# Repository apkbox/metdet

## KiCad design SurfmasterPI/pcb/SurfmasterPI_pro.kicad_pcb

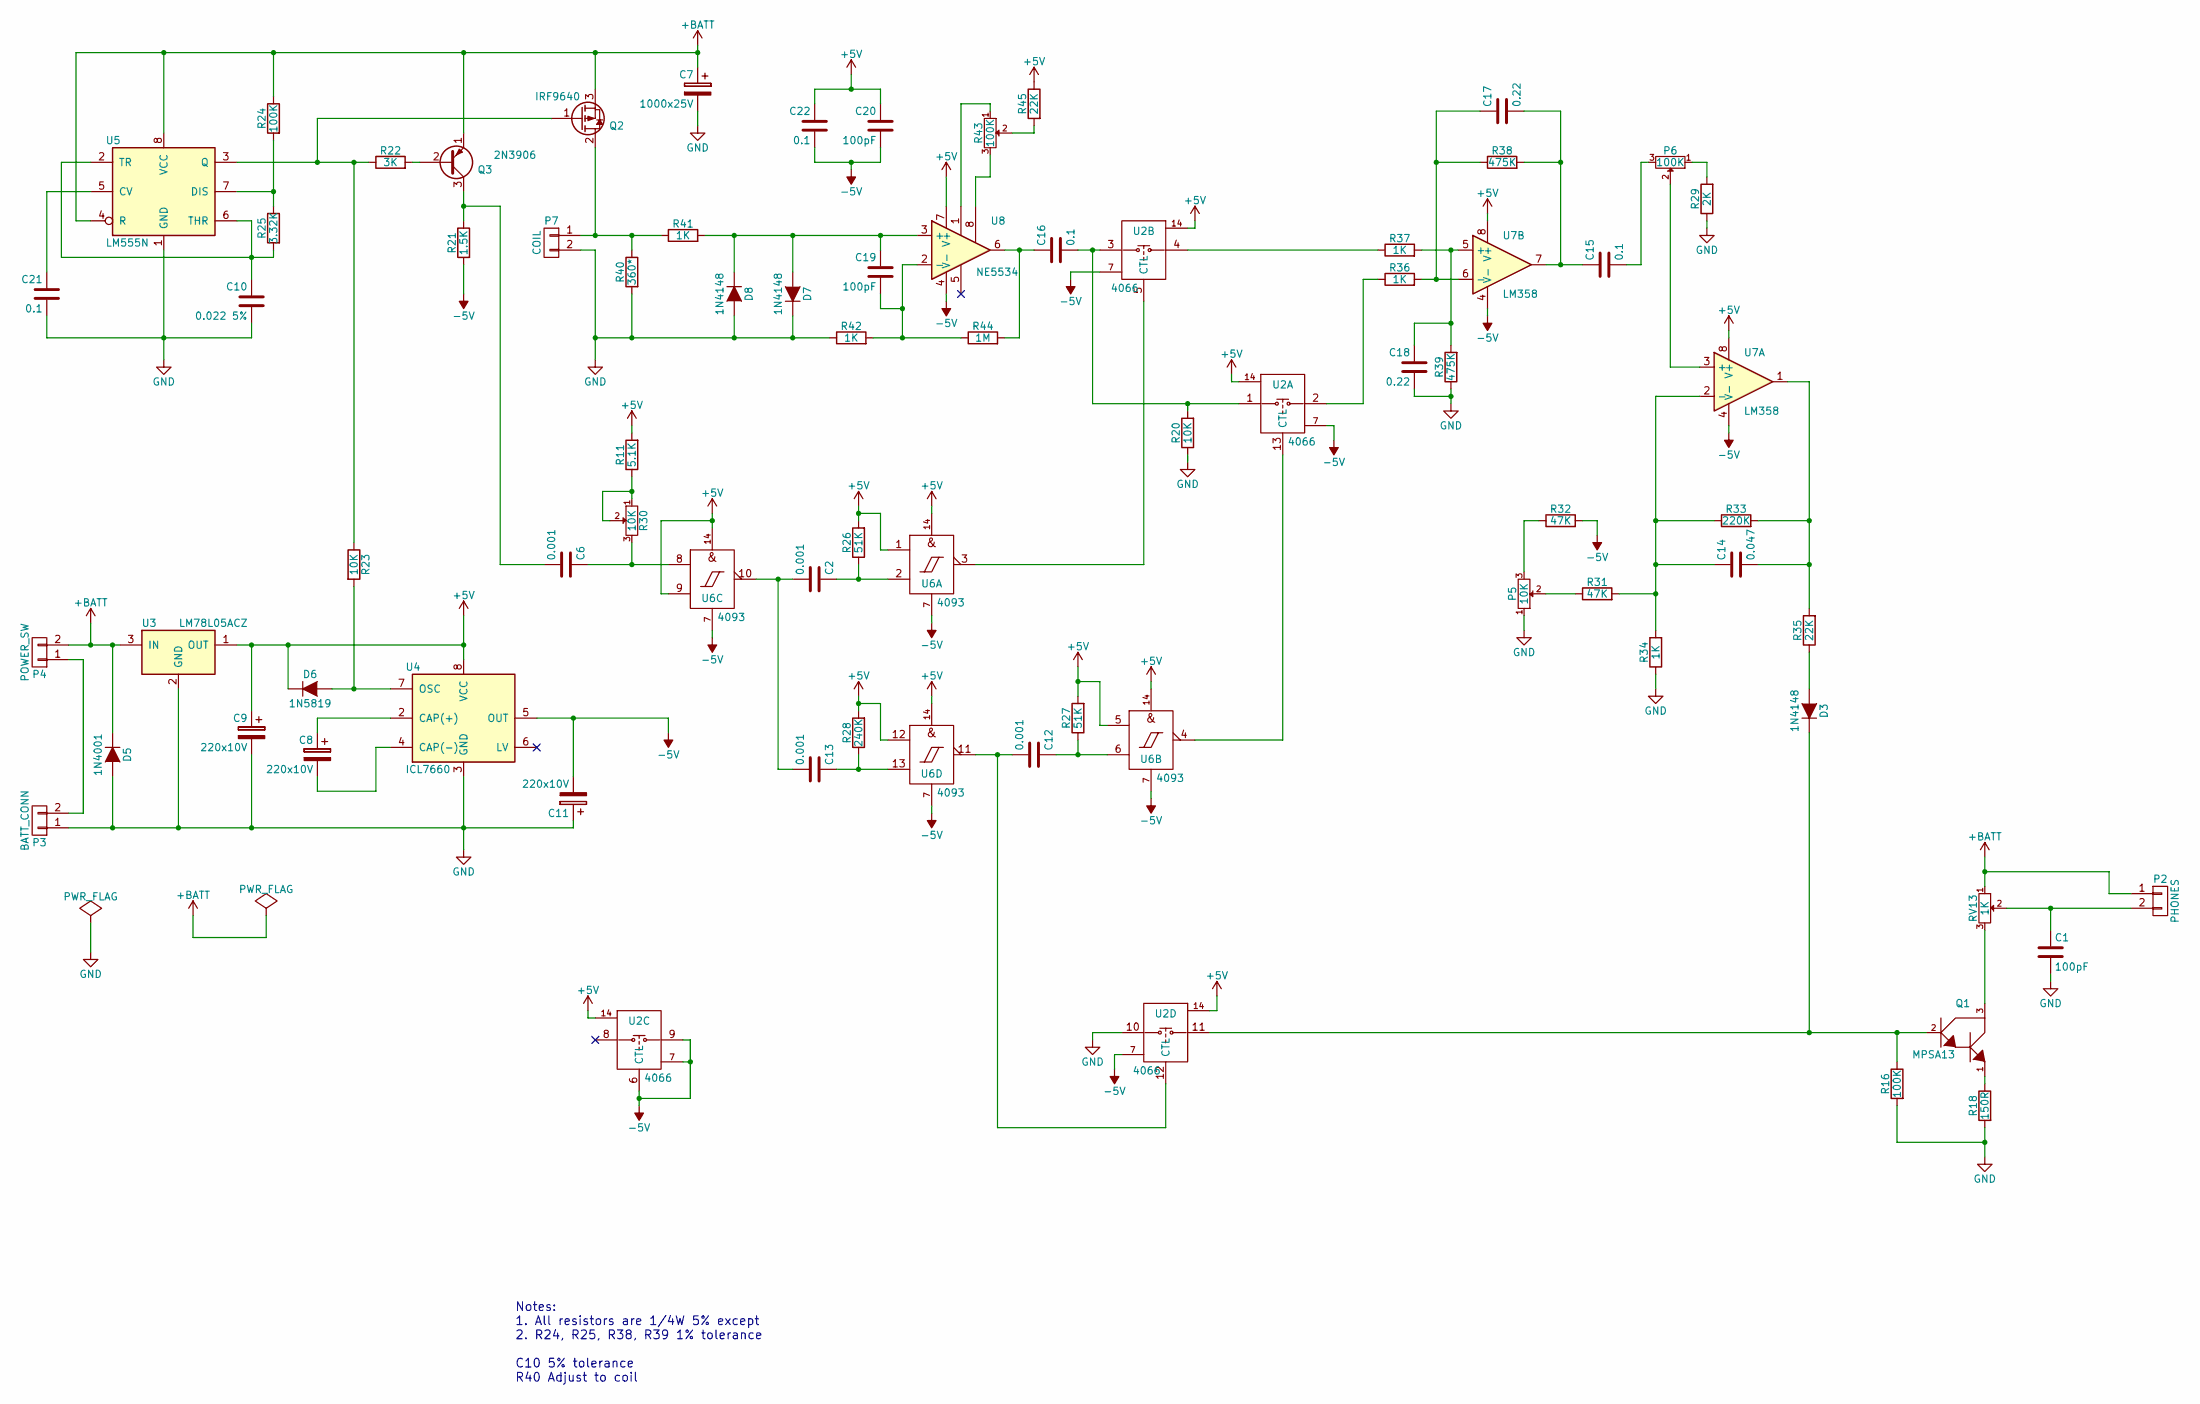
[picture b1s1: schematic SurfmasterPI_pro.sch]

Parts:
C1, C19, C20: 100pF; C_Disc_D3_P2.5
C2, C6, C12, C13: 0.001; C_Disc_D6_P5
C7: 1000x25V; C_Radial_D13_L21_P5
C8, C9, C11: 220x10V; C_Radial_D7.5_L11.2_P2.5
C10: 0.022 5%; C_Disc_D6_P5
C14: 0.047; C_Disc_D6_P5
C15, C16, C21, C22: 0.1; C_Disc_D6_P5
C17, C18: 0.22; C_Disc_D6_P5
D3, D7, D8: 1N4148; Diode_DO-41_SOD81_Horizontal_RM10
D5: 1N4001; Diode_DO-35_SOD27_Horizontal_RM10
D6: 1N5819; Diode_DO-35_SOD27_Horizontal_RM10
P2: PHONES; Pin_Header_Straight_1x02
P3: BATT_CONN; Pin_Header_Straight_1x02
P4: POWER_SW; Pin_Header_Straight_1x02
P5: 10K; Potentiometer_WirePads_Small
P6: 100K; Potentiometer_WirePads_Small
P7: COIL; Pin_Header_Straight_1x02
Q1: MPSA13; TO-92_Molded_Narrow
Q2: IRF9640; TO-220_Neutral123_Vertical_LargePads
Q3: 2N3906; TO-92_Molded_Narrow
R11: 5.1K; Resistor_Horizontal_RM10mm
R16, R24: 100K; Resistor_Horizontal_RM10mm
R18: 150R; Resistor_Horizontal_RM10mm
R20, R23: 10K; Resistor_Horizontal_RM10mm
R21: 1.5K; Resistor_Horizontal_RM10mm
R22: 3K; Resistor_Horizontal_RM10mm
R25: 3.32K; Resistor_Horizontal_RM10mm
R26, R27: 51K; Resistor_Horizontal_RM10mm
R28: 240K; Resistor_Horizontal_RM10mm
R29: 2K; Resistor_Horizontal_RM10mm
R30: 10K; Potentiometer_Trimmer-Suntan-TSR-3386P
R31, R32: 47K; Resistor_Horizontal_RM10mm
R33: 220K; Resistor_Horizontal_RM10mm
R34, R36, R37, R41, R42: 1K; Resistor_Horizontal_RM10mm
R35, R45: 22K; Resistor_Horizontal_RM10mm
R38, R39: 475K; Resistor_Horizontal_RM10mm
R40: 360*; Resistor_Horizontal_RM10mm
R43: 100K; Potentiometer_Trimmer-Suntan-TSR-3386P
R44: 1M; Resistor_Horizontal_RM10mm
RV13: 1K; Potentiometer_WirePads_Small
U2: 4066; DIP-14_W7.62mm_LongPads
U3: LM78L05ACZ; TO-92_Molded_Narrow
U4: ICL7660; DIP-8_W7.62mm_LongPads
U5: LM555N; DIP-8_W7.62mm_LongPads
U6: 4093; DIP-14_W7.62mm_LongPads
U7: LM358; DIP-8_W7.62mm_LongPads
U8: NE5534; DIP-8_W7.62mm_LongPads

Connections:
+5V: C9.1, C20.1, C22.1, D6.1 (K), R11.2, R26.2, R27.2, R28.2, R45.1, U2.14, U3.1 (OUT), U4.8 (VCC), U6.1, U6.5, U6.9, U6.12, U6.14, U7.8 (V+), U8.7 (V+)
+BATT: C7.1, D5.1 (K), P2.1, P4.2, Q2.3 (S), Q3.1 (E), R24.1, RV13.1, U3.3 (IN), U5.4 (R), U5.8 (VCC)
-5V: C11.2, C20.2, C22.2, R21.2, R32.2, U2.6 (CTL), U2.7, U2.9, U4.5 (OUT), U6.7, U7.4 (V-), U8.4 (V-)
GND: C1.2, C7.2, C9.2, C10.2, C11.1, C18.2, C21.2, D5.2 (A), D7.1 (K), D8.2 (A), P3.1, P5.1, P7.2, R16.2, R18.2, R20.1, R29.1, R34.1, R39.1, R40.2, R42.1, U2.10, U3.2 (GND), U4.3 (GND), U5.1 (GND)
unnamed: C1.1, P2.2, RV13.2
unnamed: C2.1, R26.1, U6.2
unnamed: C6.1, R30.3, U6.8
unnamed: C6.2, Q3.3 (C), R21.1
unnamed: C8.1, U4.2 (CAP(+))
unnamed: C8.2, U4.4 (CAP(-))
unnamed: C10.1, R25.2, U5.2 (TR), U5.6 (THR)
unnamed: C12.1, R27.1, U6.6
unnamed: C12.2, U2.12 (CTL), U6.11
unnamed: C13.1, R28.1, U6.13
unnamed: C2.2, C13.2, U6.10
unnamed: C14.1, R31.2, R33.1, R34.2, U7.2 (-)
unnamed: C14.2, R33.2, R35.2, U7.1
unnamed: C15.1, C17.2, R38.2, U7.7
unnamed: C15.2, P6.3
unnamed: C16.1, R44.2, U8.6
unnamed: C16.2, R20.2, U2.1, U2.3
unnamed: C17.1, R36.2, R38.1, U7.6 (-)
unnamed: C18.1, R37.2, R39.2, U7.5 (+)
unnamed: C19.1, D7.2 (A), D8.1 (K), R41.2, U8.3 (+)
unnamed: C19.2, R42.2, R44.1, U8.2 (-)
unnamed: C21.1, U5.5 (CV)
unnamed: D3.1 (K), Q1.2, R16.1, U2.11
unnamed: D3.2 (A), R35.1
unnamed: D6.2 (A), R23.2, U4.7 (OSC)
unnamed: P3.2, P4.1
unnamed: P5.2, R31.1
unnamed: P5.3, R32.1
unnamed: P6.1, R29.2
unnamed: P6.2, U7.3 (+)
unnamed: P7.1, Q2.2 (D), R40.1, R41.1
unnamed: Q1.1, R18.1
unnamed: Q1.3, RV13.3
unnamed: Q2.1 (G), R22.1, R23.1, U5.3 (Q)
unnamed: Q3.2 (B), R22.2
unnamed: R11.1, R30.1, R30.2
unnamed: R24.2, R25.1, U5.7 (DIS)
unnamed: R36.1, U2.2
unnamed: R37.1, U2.4
unnamed: R43.1, U8.1
unnamed: R43.2, R45.2
unnamed: R43.3, U8.8
unnamed: U2.5 (CTL), U6.3
unnamed: U2.13 (CTL), U6.4

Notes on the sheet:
Notes: 1. All resistors are 1/4W 5% except 2. R24, R25, R38, R39 1% tolerance C10 5% tolerance R40 Adjust to coil

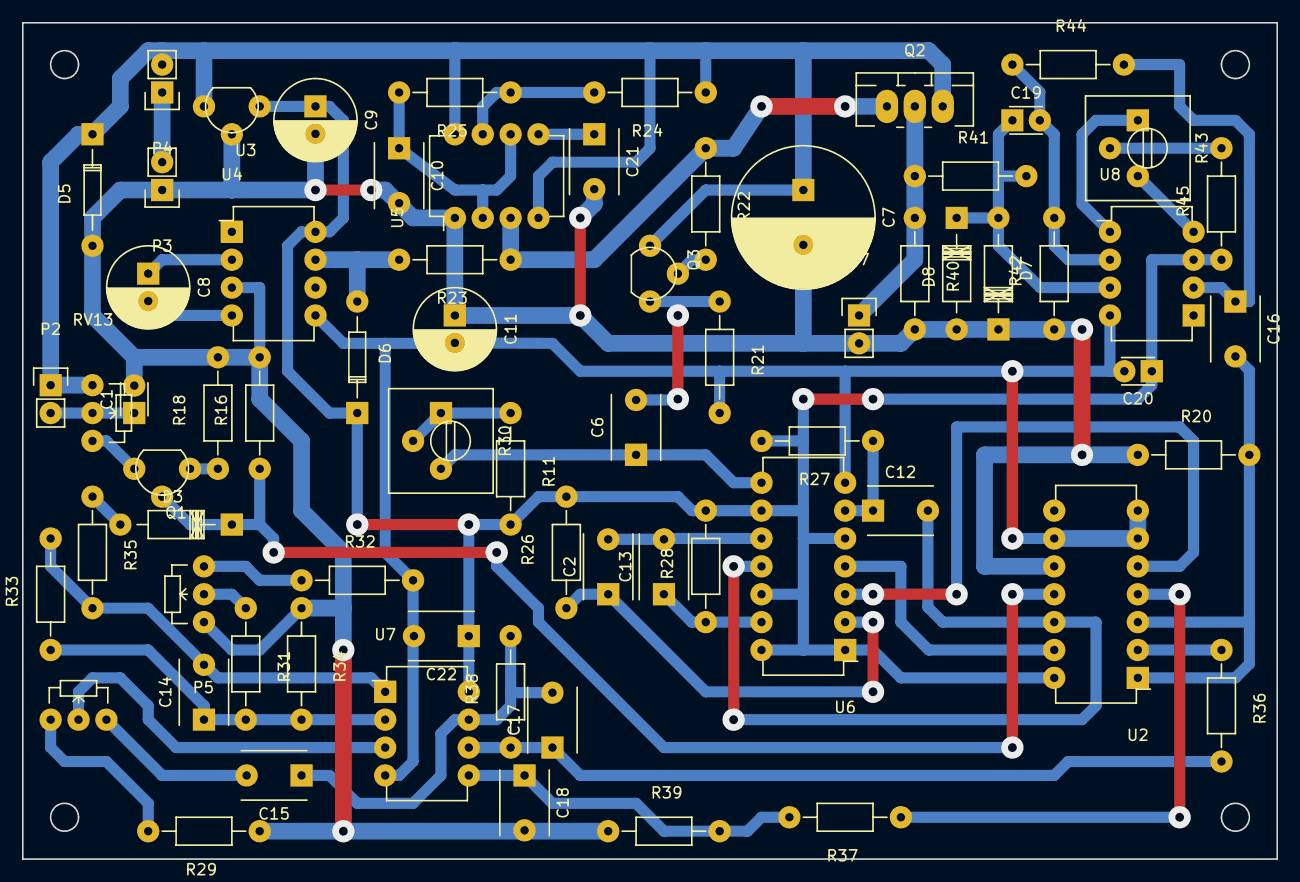
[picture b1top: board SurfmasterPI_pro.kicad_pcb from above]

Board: 2 copper layers, 114.3 x 76.2 mm, 70 parts (0 on the bottom side), 48 nets.

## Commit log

2016-08-28 Initial commit.
2016-08-28 Some changes.
2016-08-28 Added patent. Changed TO-92 footprint to compact one.
2016-08-29 Finished first version of PCB layout for pro.
2016-08-29 Updated PCB holes and pads for low res fabrication.
2016-09-06 Added detailed instructions from costa.
2016-09-07 Fixed missing trace from +5 to 4093 pin 12.
